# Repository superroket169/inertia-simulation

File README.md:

# inertia-simulation

2DOF motion simulator rig driven by DC motors.

- **PC side:** [FlyPT Mover](https://www.flyptmover.com) reads game telemetry and sends SMC3 frames (`[A hi lo][B hi lo]`) over serial.
- **`firmware/`:** Arduino Nano (ATmega328P) controller in plain C: SMC3 parser, PID position loop, HOA/fault handling. Build with `make`, flash with `make flash`, run parser tests with `make test`. Rig-specific values are in `firmware/config.h`.
- **`hardware/`, `mafsal/`, `Bağlantı_Ekipmanları/`:** CAD and electronics files.
- **`core/` (legacy):** C++/raylib wheel input and Linux force-feedback experiments. Not part of the motion rig; kept for reference.

Open work is tracked in GitHub issues.

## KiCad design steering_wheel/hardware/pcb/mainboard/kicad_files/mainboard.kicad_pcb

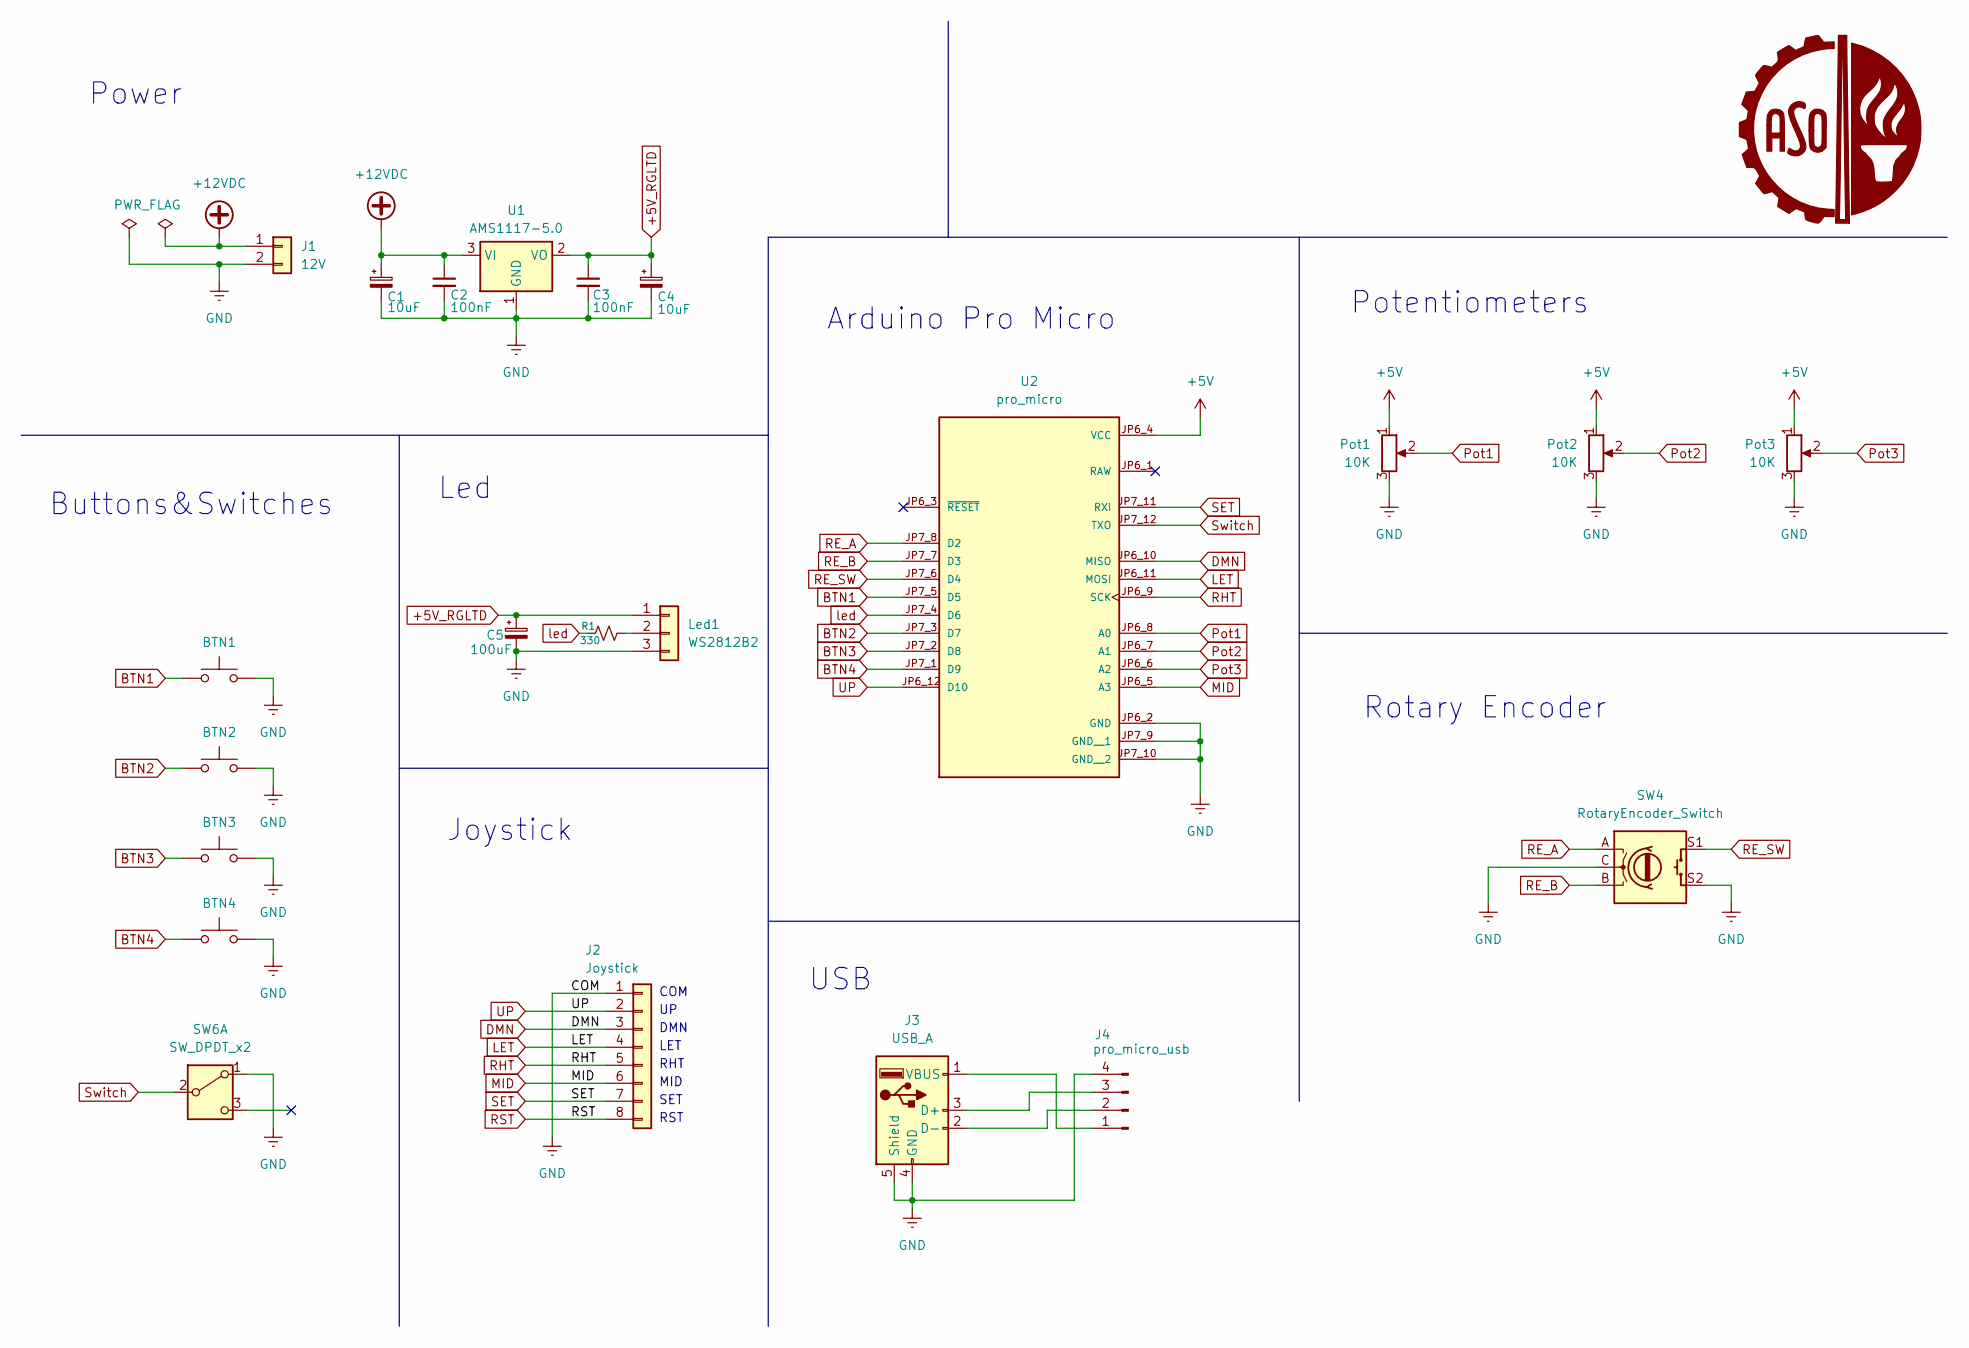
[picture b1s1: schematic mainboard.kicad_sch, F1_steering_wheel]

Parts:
C1, C4: 10uF; CP_Radial_D5.0mm_P2.50mm
C2, C3: 100nF; C_Disc_D8.0mm_W2.5mm_P5.00mm
C5: 100uF; CP_Radial_D5.0mm_P2.50mm
J1: 12V; JST_EH_B2B-EH-A_1x02_P2.50mm_Vertical
J2: Joystick; JST_EH_B8B-EH-A_1x08_P2.50mm_Vertical
J3: USB_A; JST_EH_B4B-EH-A_1x04_P2.50mm_Vertical
J4: pro_micro_usb; PinHeader_1x04_P2.54mm_Vertical
Led1: WS2812B2; JST_EH_B3B-EH-A_1x03_P2.50mm_Vertical
Pot1, Pot2, Pot3: 10K; JST_EH_B3B-EH-A_1x03_P2.50mm_Vertical
R1: 330; R_Axial_DIN0207_L6.3mm_D2.5mm_P7.62mm_Horizontal
SW1: BTN1; JST_EH_B2B-EH-A_1x02_P2.50mm_Vertical
SW2: BTN2; JST_EH_B2B-EH-A_1x02_P2.50mm_Vertical
SW3: BTN3; JST_EH_B2B-EH-A_1x02_P2.50mm_Vertical
SW4: RotaryEncoder_Switch; rotary_connector
SW5: BTN4; JST_EH_B2B-EH-A_1x02_P2.50mm_Vertical
SW6: SW_DPDT_x2; JST_EH_B3B-EH-A_1x03_P2.50mm_Vertical
U1: AMS1117-5.0; SOT-223-3_TabPin2
U2: pro_micro

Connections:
+5V: Pot1.1, Pot2.1, Pot3.1, U2.JP6_4 (VCC)
+5V_RGLTD: C3.1, C4.1, C5.1, Led1.1, U1.2 (VO)
+12VDC: C1.1, C2.1, J1.1, U1.3 (VI)
BTN1: SW1.1, U2.JP7_5 (D5)
BTN2: SW2.1, U2.JP7_3 (D7)
BTN3: SW3.1, U2.JP7_2 (D8)
BTN4: SW5.1, U2.JP7_1 (D9)
DMN: J2.3, U2.JP6_10 (MISO)
GND: C1.2, C2.2, C3.2, C4.2, C5.2, J1.2, J2.1, J3.4 (GND), J3.5 (Shield), J4.4, Led1.3, Pot1.3, Pot2.3, Pot3.3, SW1.2, SW2.2, SW3.2, SW4.C, SW4.S2, SW5.2, SW6.1 (A), U1.1 (GND), U2.JP6_2 (GND), U2.JP7_9 (GND__1), U2.JP7_10 (GND__2)
LET: J2.4, U2.JP6_11 (MOSI)
MID: J2.6, U2.JP6_5 (A3)
unnamed: J3.3 (D+), J4.3
unnamed: J3.2 (D-), J4.2
unnamed: J3.1 (VBUS), J4.1
unnamed: Led1.2, R1.2
Pot1: Pot1.2, U2.JP6_8 (A0)
Pot2: Pot2.2, U2.JP6_7 (A1)
Pot3: Pot3.2, U2.JP6_6 (A2)
RE_A: SW4.A, U2.JP7_8 (D2)
RE_B: SW4.B, U2.JP7_7 (D3)
RE_SW: SW4.S1, U2.JP7_6 (D4)
RHT: J2.5, U2.JP6_9 (SCK)
RST: J2.8
SET: J2.7, U2.JP7_11 (RXI)
Switch: SW6.2 (B), U2.JP7_12 (TXO)
UP: J2.2, U2.JP6_12 (D10)
led: R1.1, U2.JP7_4 (D6)

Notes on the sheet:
USB
COM
LET
Potentiometers
RHT
SET
RST
Rotary Encoder
Led
Arduino Pro Micro
Joystick
MID
Power
DMN
Buttons&Switches

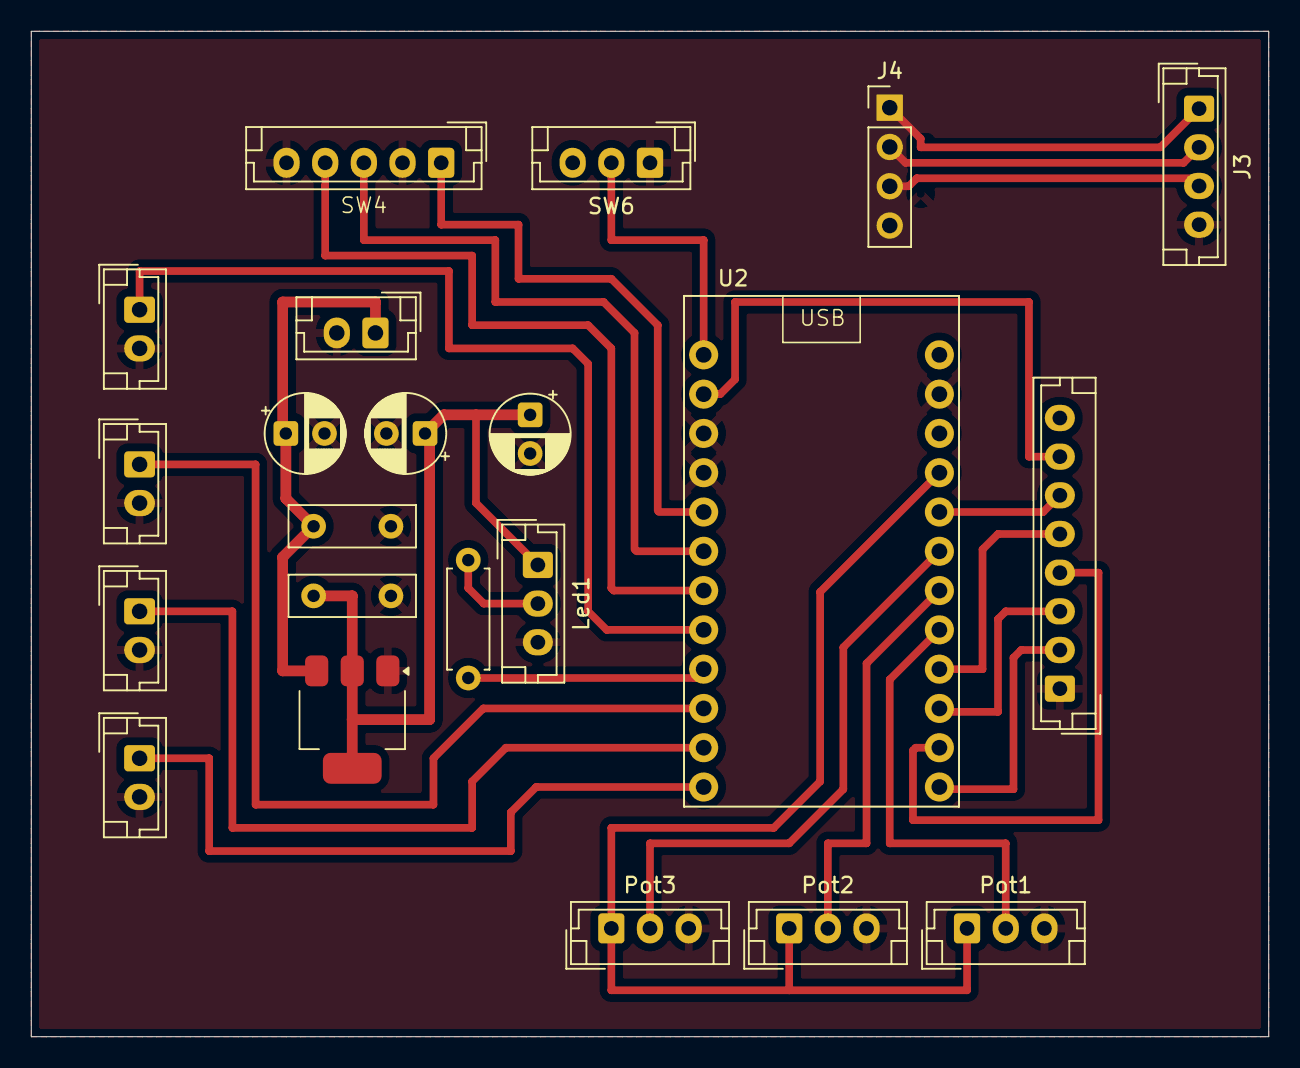
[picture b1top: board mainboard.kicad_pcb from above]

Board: 2 copper layers, 80.0 x 65.0 mm, 22 parts (0 on the bottom side), 26 nets.

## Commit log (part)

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2026-01-08 docs: add CONTRIBUTION.md
2026-01-08 wip: add HardwareInput namespace
2026-01-08 wip: add input.h template
2026-01-08 solidworks parçaları
    add sldrt 3d files
2026-01-11 feat: replace wec steering wheel file with updated pcb and 3d design files
2026-01-11 version 1.0 for F1 steering wheel
2026-01-11 simualtion code
2026-01-12 system fix: delete src
2026-01-12 docs: document system fixed
2026-01-12 dics: fixed documents more
2026-01-12 wip: calibration add
2026-01-12 feat: linux_ff library helper
2026-01-13 feat: input header/lib and testgui
2026-01-13 feat: basic car sim
2026-01-23 quick relase system
    parts used in the quick relase system of the steering wheel
2026-05-30 added renders
2026-05-30 bağlantı ekipmanları
2026-05-30 mafsal
2026-05-30 eski direksiyon
